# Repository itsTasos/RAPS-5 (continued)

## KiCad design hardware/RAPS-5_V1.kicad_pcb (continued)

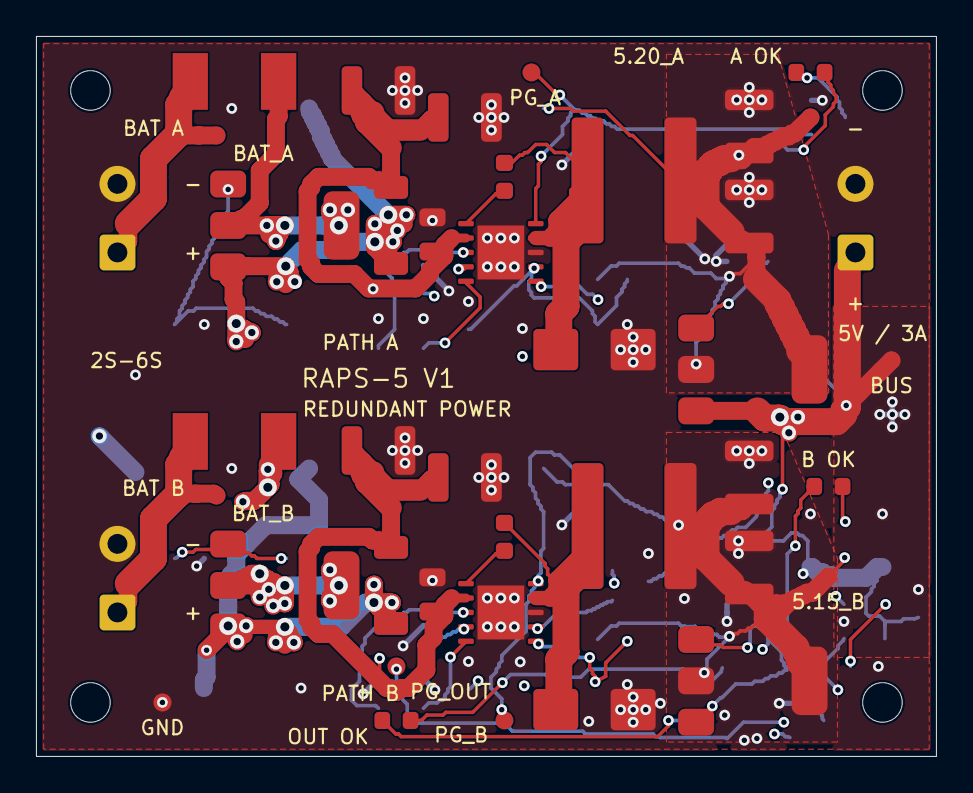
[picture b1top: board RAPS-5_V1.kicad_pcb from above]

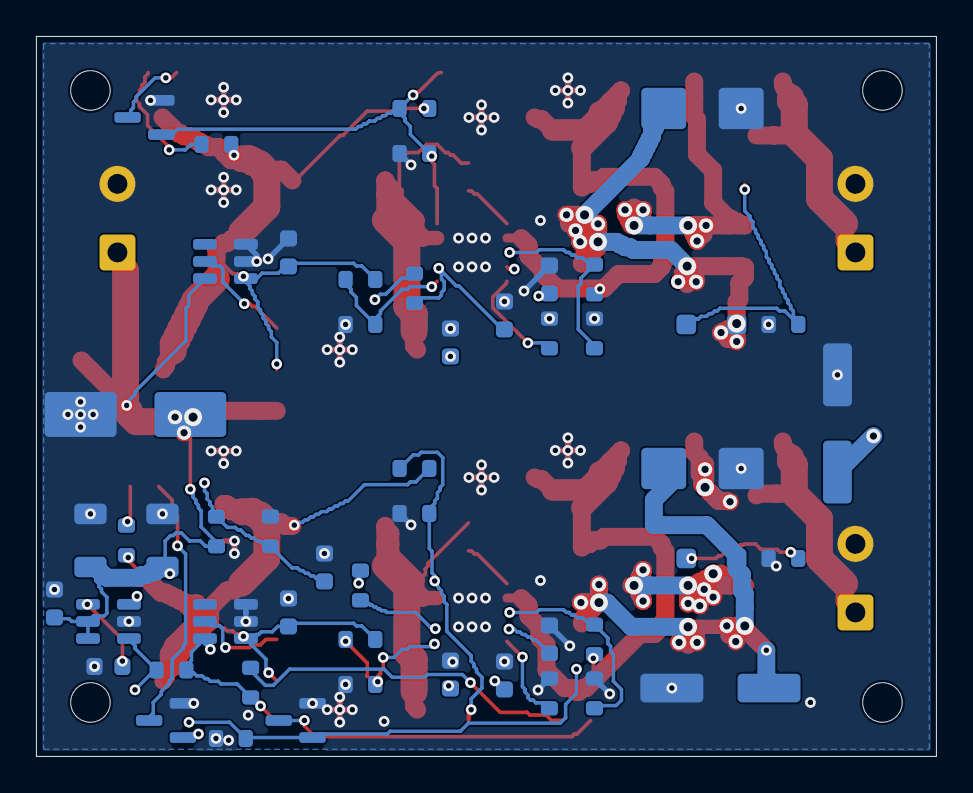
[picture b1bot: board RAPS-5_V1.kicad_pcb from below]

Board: 4 copper layers, 50.0 x 40.0 mm, 96 parts (51 on the bottom side), 43 nets.

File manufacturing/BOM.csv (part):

Reference,Value,MPN,Footprint,Description,Datasheet
J1,BAT A / 2S-6S,1727010,TerminalBlock_Phoenix:TerminalBlock_Phoenix_MKDS-1-2-3.81_1x02_P3.81mm_Horizontal,"Phoenix MKDS 1/2-3.81; 3.81mm pitch, 10A; pin1 positive, pin2 GND",
F1,5A / 125V,0451005.MRL,Fuse:Fuse_Littelfuse-NANO2-451_453,Fast 5A single-use fuse,
Q1,DMP6023LE / 60V,DMP6023LE-13,Package_TO_SOT_SMD:SOT-223-3_TabPin2,"Reverse polarity: drain upstream, source downstream",https://www.diodes.com/datasheet/download/DMP6023LE.pdf
D1,12V / BZT52H-C12,BZT52H-C12,Diode_SMD:D_SOD-123F,VGS clamp: cathode at source,
R1,47k,RC0603FR-0747KL,Resistor_SMD:R_0603_1608Metric,,
D2,SMBJ26CA / 600W,SMBJ26CA,Diode_SMD:D_SMB,"26V stand-off, max clamp 42.1V",https://www.littelfuse.com/assetdocs/littelfuse-tvs-diode-sm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
FB1,60R@100MHz / 6A,742792410,Inductor_SMD:L_1806_4516Metric,High-current 1806 bead; DCR 10mR; verify impedance under DC bias,
C1,22uF / 50V,EEE-FK1H220P,Capacitor_SMD:CP_Elec_6.3x7.7,Damped input bulk before bead,
C2,4.7uF / 50V X7R,GRM32ER71H475KA88L,Capacitor_SMD:C_1210_3225Metric,Local high-voltage ceramic input,
C3,4.7uF / 50V X7R,GRM32ER71H475KA88L,Capacitor_SMD:C_1210_3225Metric,Local high-voltage ceramic input,
C4,2.2uF / 50V X7R,GRM21BR71H225KA12L,Capacitor_SMD:C_0805_2012Metric,Local input bypass directly beside VIN; retain 50V rating,
U1,TPS54561DPRR,TPS54561DPRR,Package_SON:WSON-10-1EP_4x4mm_P0.8mm_EP2.6x3mm,60V 5A buck; exposed pad to GND,https://www.ti.com/lit/ds/symlink/tps54561.pdf
C5,100nF / 16V,GRM188R71C104KA01D,Capacitor_SMD:C_0603_1608Metric,Bootstrap capacitor directly at IC,
D3,STPS5L60U / 5A 60V,STPS5L60U,Diode_SMD:D_SMB,"Catch diode, cathode at SW",https://www.st.com/resource/en/datasheet/stps5l60.pdf
L1,10uH / XAL8080,XAL8080-103MED,Inductor_SMD:L_Coilcraft_XAL8080-XXX,"Shielded, Isat >=8.8A, Irms >=6A",https://www.coilcraft.com/en-us/products/power/shielded-indu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
C6,47uF / 16V X5R,GRM32ER61C476KE15L,Capacitor_SMD:C_1210_3225Metric,Require effective >=30uF at 5.2V per capacitor,
C7,47uF / 16V X5R,GRM32ER61C476KE15L,Capacitor_SMD:C_1210_3225Metric,Require effective >=30uF at 5.2V per capacitor,
R2,100k,,Resistor_SMD:R_0603_1608Metric,,
R3,22k,,Resistor_SMD:R_0603_1608Metric,,
R4,249k,,Resistor_SMD:R_0603_1608Metric,,
R5,55.0k 0.1%,,Resistor_SMD:R_0603_1608Metric,,
R6,10.0k 0.1%,,Resistor_SMD:R_0603_1608Metric,,
R7,10.0k,,Resistor_SMD:R_0603_1608Metric,,
C8,10nF / 25V,GRM188R71E103KA01D,Capacitor_SMD:C_0603_1608Metric,Independent soft-start,
C9,22nF / 25V,GRM188R71E223KA01D,Capacitor_SMD:C_0603_1608Metric,Conservative Type II zero ~723Hz; bench validate,
C10,220pF / 50V C0G,GRM1885C1H221JA01D,Capacitor_SMD:C_0603_1608Metric,,
Q2,DMP6023LE / 60V,DMP6023LE-13,Package_TO_SOT_SMD:SOT-223-3_TabPin2,"Ideal diode: drain at channel, source at BUS",https://www.diodes.com/datasheet/download/DMP6023LE.pdf
U2,LTC4412ES6#TRPBF,LTC4412ES6#TRPBF,Package_TO_SOT_SMD:TSOT-23-6,CTL grounded; STAT intentionally unused,https://www.analog.com/media/en/technical-documentation/data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
C11,100nF / 16V,GRM188R71C104KA01D,Capacitor_SMD:C_0603_1608Metric,,
R8,10k,,Resistor_SMD:R_0603_1608Metric,,
R9,100k,,Resistor_SMD:R_0603_1608Metric,,
Q3,2N7002,2N7002-7-F,Package_TO_SOT_SMD:SOT-23,N-MOS LED buffer,https://www.onsemi.com/pub/Collateral/NDS7002A-D.PDF
R10,2.2k,,Resistor_SMD:R_0603_1608Metric,,
D4,GREEN / PATH A OK,LTST-C190KGKT,LED_SMD:LED_0603_1608Metric,,
TP1,BAT_A,,TestPoint:TestPoint_Pad_D1.0mm,,
TP3,5.20V_A,,TestPoint:TestPoint_Pad_D1.0mm,,
J2,BAT B / 2S-6S,1727010,TerminalBlock_Phoenix:TerminalBlock_Phoenix_MKDS-1-2-3.81_1x02_P3.81mm_Horizontal,"Phoenix MKDS 1/2-3.81; 3.81mm pitch, 10A; pin1 positive, pin2 GND",
F101,5A / 125V,0451005.MRL,Fuse:Fuse_Littelfuse-NANO2-451_453,Fast 5A single-use fuse,
Q101,DMP6023LE / 60V,DMP6023LE-13,Package_TO_SOT_SMD:SOT-223-3_TabPin2,"Reverse polarity: drain upstream, source downstream",https://www.diodes.com/datasheet/download/DMP6023LE.pdf
D101,12V / BZT52H-C12,BZT52H-C12,Diode_SMD:D_SOD-123F,VGS clamp: cathode at source,
R101,47k,RC0603FR-0747KL,Resistor_SMD:R_0603_1608Metric,,
D102,SMBJ26CA / 600W,SMBJ26CA,Diode_SMD:D_SMB,"26V stand-off, max clamp 42.1V",https://www.littelfuse.com/assetdocs/littelfuse-tvs-diode-sm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
FB101,60R@100MHz / 6A,742792410,Inductor_SMD:L_1806_4516Metric,High-current 1806 bead; DCR 10mR; verify impedance under DC bias,
C101,22uF / 50V,EEE-FK1H220P,Capacitor_SMD:CP_Elec_6.3x7.7,Damped input bulk before bead,
C102,4.7uF / 50V X7R,GRM32ER71H475KA88L,Capacitor_SMD:C_1210_3225Metric,Local high-voltage ceramic input,
C103,4.7uF / 50V X7R,GRM32ER71H475KA88L,Capacitor_SMD:C_1210_3225Metric,Local high-voltage ceramic input,
C104,2.2uF / 50V X7R,GRM21BR71H225KA12L,Capacitor_SMD:C_0805_2012Metric,Local input bypass directly beside VIN; retain 50V rating,
U101,TPS54561DPRR,TPS54561DPRR,Package_SON:WSON-10-1EP_4x4mm_P0.8mm_EP2.6x3mm,60V 5A buck; exposed pad to GND,https://www.ti.com/lit/ds/symlink/tps54561.pdf
C105,100nF / 16V,GRM188R71C104KA01D,Capacitor_SMD:C_0603_1608Metric,Bootstrap capacitor directly at IC,
D103,STPS5L60U / 5A 60V,STPS5L60U,Diode_SMD:D_SMB,"Catch diode, cathode at SW",https://www.st.com/resource/en/datasheet/stps5l60.pdf
L101,10uH / XAL8080,XAL8080-103MED,Inductor_SMD:L_Coilcraft_XAL8080-XXX,"Shielded, Isat >=8.8A, Irms >=6A",https://www.coilcraft.com/en-us/products/power/shielded-indu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
C106,47uF / 16V X5R,GRM32ER61C476KE15L,Capacitor_SMD:C_1210_3225Metric,Require effective >=30uF at 5.2V per capacitor,
C107,47uF / 16V X5R,GRM32ER61C476KE15L,Capacitor_SMD:C_1210_3225Metric,Require effective >=30uF at 5.2V per capacitor,
R102,100k,,Resistor_SMD:R_0603_1608Metric,,
R103,22k,,Resistor_SMD:R_0603_1608Metric,,
R104,249k,,Resistor_SMD:R_0603_1608Metric,,
R105,54.4k 0.1%,,Resistor_SMD:R_0603_1608Metric,,
R106,10.0k 0.1%,,Resistor_SMD:R_0603_1608Metric,,
R107,10.0k,,Resistor_SMD:R_0603_1608Metric,,
C108,10nF / 25V,GRM188R71E103KA01D,Capacitor_SMD:C_0603_1608Metric,Independent soft-start,
C109,22nF / 25V,GRM188R71E223KA01D,Capacitor_SMD:C_0603_1608Metric,Conservative Type II zero ~723Hz; bench validate,
C110,220pF / 50V C0G,GRM1885C1H221JA01D,Capacitor_SMD:C_0603_1608Metric,,
Q102,DMP6023LE / 60V,DMP6023LE-13,Package_TO_SOT_SMD:SOT-223-3_TabPin2,"Ideal diode: drain at channel, source at BUS",https://www.diodes.com/datasheet/download/DMP6023LE.pdf
U102,LTC4412ES6#TRPBF,LTC4412ES6#TRPBF,Package_TO_SOT_SMD:TSOT-23-6,CTL grounded; STAT intentionally unused,https://www.analog.com/media/en/technical-documentation/data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
C111,100nF / 16V,GRM188R71C104KA01D,Capacitor_SMD:C_0603_1608Metric,,
R108,10k,,Resistor_SMD:R_0603_1608Metric,,
R109,100k,,Resistor_SMD:R_0603_1608Metric,,
Q103,2N7002,2N7002-7-F,Package_TO_SOT_SMD:SOT-23,N-MOS LED buffer,https://www.onsemi.com/pub/Collateral/NDS7002A-D.PDF
R110,2.2k,,Resistor_SMD:R_0603_1608Metric,,
D104,GREEN / PATH B OK,LTST-C190KGKT,LED_SMD:LED_0603_1608Metric,,
TP2,BAT_B,,TestPoint:TestPoint_Pad_D1.0mm,,
TP4,5.15V_B,,TestPoint:TestPoint_Pad_D1.0mm,,
J3,AVIONICS 5V / 3A,1727010,TerminalBlock_Phoenix:TerminalBlock_Phoenix_MKDS-1-2-3.81_1x02_P3.81mm_Horizontal,"Phoenix MKDS 1/2-3.81; 3.81mm pitch, 10A; pin1 positive, pin2 GND",
C201,220uF / 10V polymer,10SVPF220M,Capacitor_SMD:CP_Elec_8x6.7,Low ESR 220uF bulk; ripple rating >=3A,
C202,22uF / 16V X5R,GRM31CR61C226KE15L,Capacitor_SMD:C_1206_3216Metric,,
C203,22uF / 16V X5R,GRM31CR61C226KE15L,Capacitor_SMD:C_1206_3216Metric,,
U201,TPS3808G01DBVR,TPS3808G01DBVR,Package_TO_SOT_SMD:SOT-23-6,"Adjustable output supervisor, threshold 4.93V",http://www.ti.com/lit/ds/symlink/tps3808.pdf
R201,112k 0.1%,,Resistor_SMD:R_0603_1608Metric,,
R202,10.0k 0.1%,,Resistor_SMD:R_0603_1608Metric,,
R203,10k,,Resistor_SMD:R_0603_1608Metric,,
R204,100k,,Resistor_SMD:R_0603_1608Metric,,
R205,2.2k,,Resistor_SMD:R_0603_1608Metric,,
C204,100nF / 16V,,Capacitor_SMD:C_0603_1608Metric,,
C205,1nF / 50V,,Capacitor_SMD:C_0603_1608Metric,,
C206,1nF / 50V,,Capacitor_SMD:C_0603_1608Metric,,
Q201,2N7002,2N7002-7-F,Package_TO_SOT_SMD:SOT-23,,https://www.onsemi.com/pub/Collateral/NDS7002A-D.PDF
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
